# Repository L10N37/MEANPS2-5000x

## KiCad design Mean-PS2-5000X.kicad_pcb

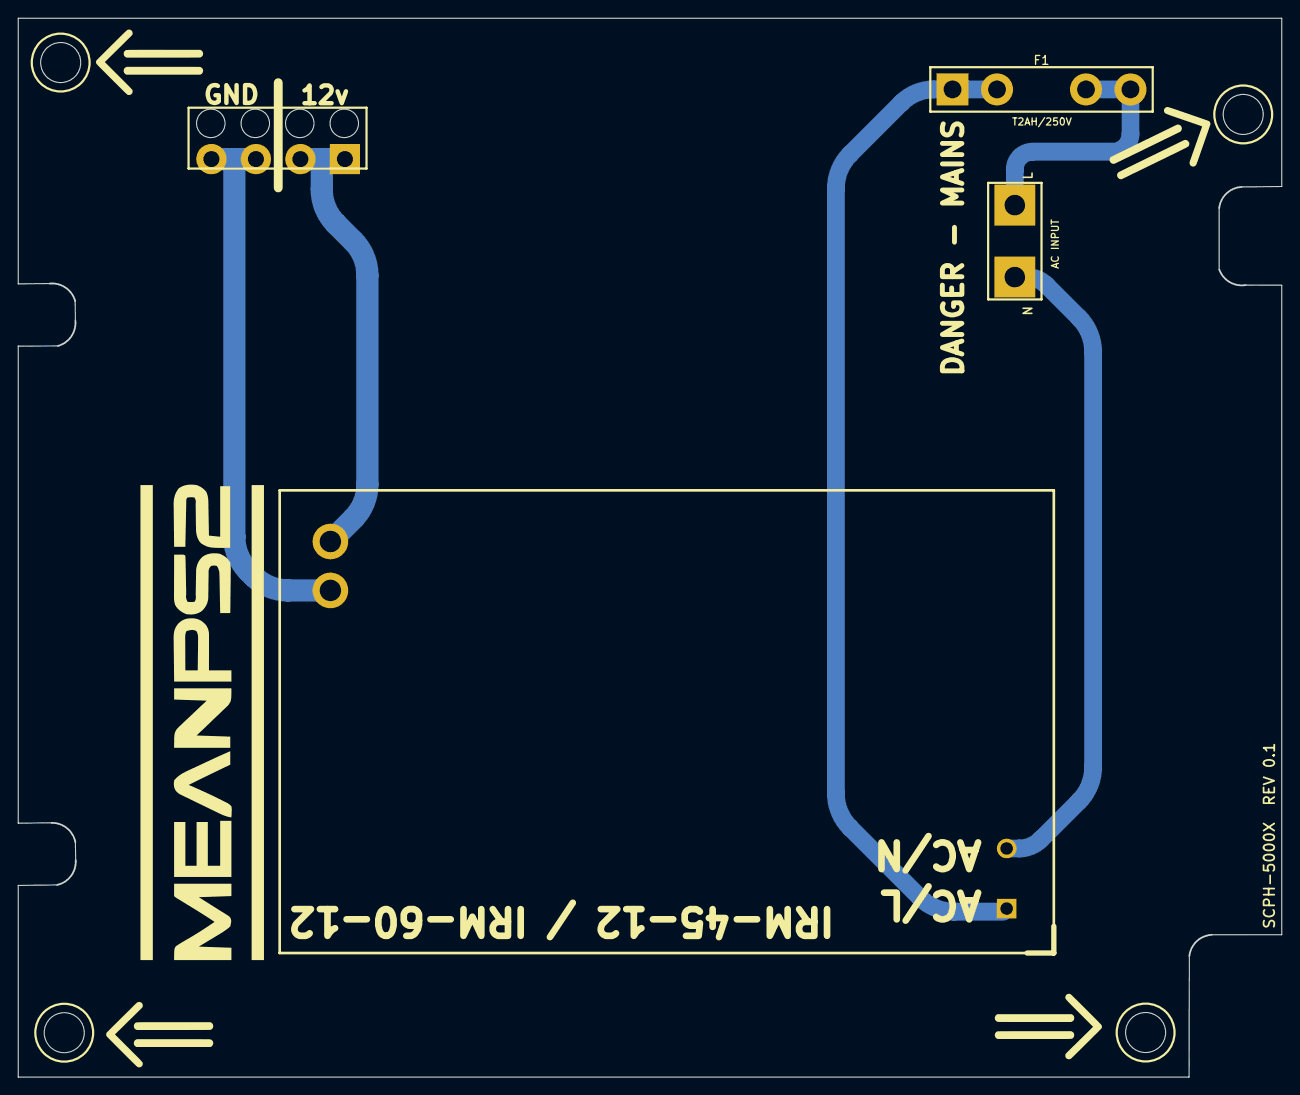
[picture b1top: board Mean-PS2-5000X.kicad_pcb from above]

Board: 2 copper layers, 142.0 x 119.0 mm, 8 parts (0 on the bottom side), 5 nets.

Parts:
F1: T2AH/250V; Sony_Fuseholder_5x20_4Pin
H1, H2, H3, H4: MOUNTING HOLE 4.5; MountingHole_4.5mm_NPTH
J1: AC INPUT; Sony_AC_Input_2Pin_8.5mm
J2: PS2 12V OUT; Sony_PS2_Output_4Pin_20mm
U1: IRM-45-12 / IRM-60-12; IRM-45_60_PCB

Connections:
+12V: J2.3 (+12V), J2.4 (+12V), U1.4 (+V)
AC_L_FUSED: F1.1 (FUSED), U1.1 (AC/L)
AC_L_IN: F1.2 (LINE), J1.1 (LIVE)
AC_N: J1.2 (NEUTRAL), U1.2 (AC/N)
GND: J2.1 (GND), J2.2 (GND), U1.3 (-V)
